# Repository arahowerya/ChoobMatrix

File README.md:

# ChoobMatrix
Source code for PIC16F722A nixie tube drivers

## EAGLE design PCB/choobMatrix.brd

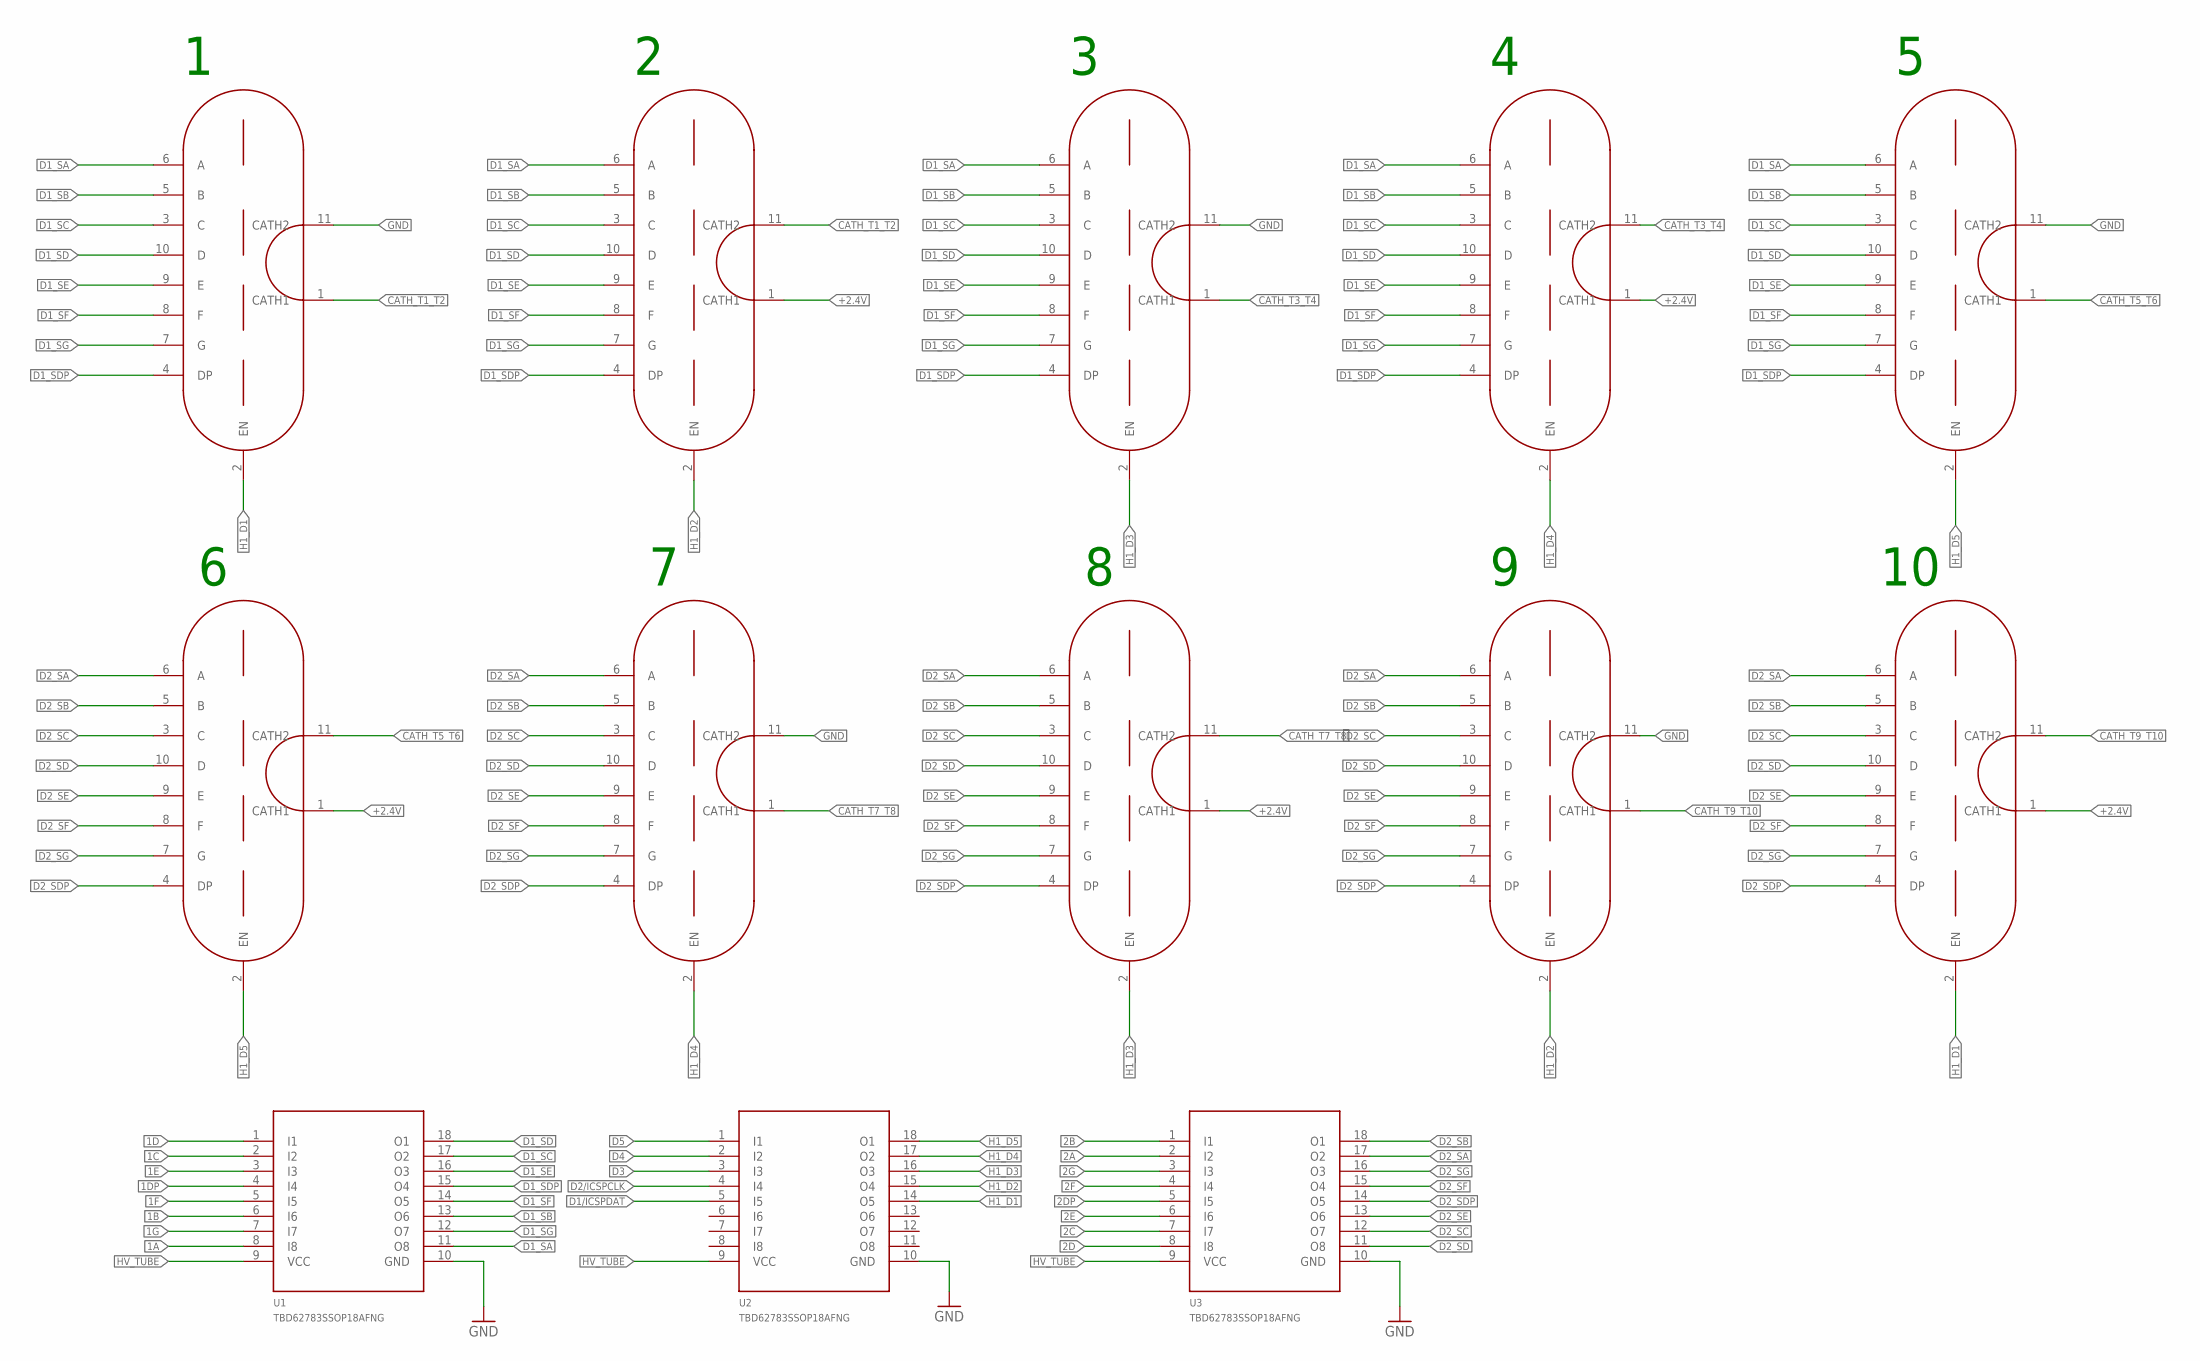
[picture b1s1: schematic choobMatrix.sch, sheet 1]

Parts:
T1, T2, T3, T4, T5, T6, T7, T8, T9, T10: IV11
U1, U2, U3: TBD62783SSOP18AFNG; SOP65P640X15-18

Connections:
1A: U1.8 (I8); also elsewhere on the board
1B: U1.6 (I6); also elsewhere on the board
1C: U1.2 (I2); also elsewhere on the board
1D: U1.1 (I1); also elsewhere on the board
1DP: U1.4 (I4); also elsewhere on the board
1E: U1.3 (I3); also elsewhere on the board
1F: U1.5 (I5); also elsewhere on the board
1G: U1.7 (I7); also elsewhere on the board
2A: U3.2 (I2); also elsewhere on the board
2B: U3.1 (I1); also elsewhere on the board
2C: U3.7 (I7); also elsewhere on the board
2D: U3.8 (I8); also elsewhere on the board
2DP: U3.5 (I5); also elsewhere on the board
2E: U3.6 (I6); also elsewhere on the board
2F: U3.4 (I4); also elsewhere on the board
2G: U3.3 (I3); also elsewhere on the board
+2.4V: T2.1 (CATH1), T4.1 (CATH1), T6.1 (CATH1), T8.1 (CATH1), T10.1 (CATH1); also elsewhere on the board
CATH_T1_T2: T1.1 (CATH1), T2.11 (CATH2)
CATH_T3_T4: T3.1 (CATH1), T4.11 (CATH2)
CATH_T5_T6: T5.1 (CATH1), T6.11 (CATH2)
CATH_T7_T8: T7.1 (CATH1), T8.11 (CATH2)
CATH_T9_T10: T9.1 (CATH1), T10.11 (CATH2)
D1/ICSPDAT: U2.5 (I5); also elsewhere on the board
D1_SA: T1.6 (A), T2.6 (A), T3.6 (A), T4.6 (A), T5.6 (A), U1.11 (O8)
D1_SB: T1.5 (B), T2.5 (B), T3.5 (B), T4.5 (B), T5.5 (B), U1.13 (O6)
D1_SC: T1.3 (C), T2.3 (C), T3.3 (C), T4.3 (C), T5.3 (C), U1.17 (O2)
D1_SD: T1.10 (D), T2.10 (D), T3.10 (D), T4.10 (D), T5.10 (D), U1.18 (O1)
D1_SDP: T1.4 (DP), T2.4 (DP), T3.4 (DP), T4.4 (DP), T5.4 (DP), U1.15 (O4)
D1_SE: T1.9 (E), T2.9 (E), T3.9 (E), T4.9 (E), T5.9 (E), U1.16 (O3)
D1_SF: T1.8 (F), T2.8 (F), T3.8 (F), T4.8 (F), T5.8 (F), U1.14 (O5)
D1_SG: T1.7 (G), T2.7 (G), T3.7 (G), T4.7 (G), T5.7 (G), U1.12 (O7)
D2/ICSPCLK: U2.4 (I4); also elsewhere on the board
D2_SA: T6.6 (A), T7.6 (A), T8.6 (A), T9.6 (A), T10.6 (A), U3.17 (O2)
D2_SB: T6.5 (B), T7.5 (B), T8.5 (B), T9.5 (B), T10.5 (B), U3.18 (O1)
D2_SC: T6.3 (C), T7.3 (C), T8.3 (C), T9.3 (C), T10.3 (C), U3.12 (O7)
D2_SD: T6.10 (D), T7.10 (D), T8.10 (D), T9.10 (D), T10.10 (D), U3.11 (O8)
D2_SDP: T6.4 (DP), T7.4 (DP), T8.4 (DP), T9.4 (DP), T10.4 (DP), U3.14 (O5)
D2_SE: T6.9 (E), T7.9 (E), T8.9 (E), T9.9 (E), T10.9 (E), U3.13 (O6)
D2_SF: T6.8 (F), T7.8 (F), T8.8 (F), T9.8 (F), T10.8 (F), U3.15 (O4)
D2_SG: T6.7 (G), T7.7 (G), T8.7 (G), T9.7 (G), T10.7 (G), U3.16 (O3)
D3: U2.3 (I3); also elsewhere on the board
D4: U2.2 (I2); also elsewhere on the board
D5: U2.1 (I1); also elsewhere on the board
GND: T1.11 (CATH2), T3.11 (CATH2), T5.11 (CATH2), T7.11 (CATH2), T9.11 (CATH2), U1.10 (GND), U2.10 (GND), U3.10 (GND); also elsewhere on the board
H1_D1: T1.2 (EN), T10.2 (EN), U2.14 (O5)
H1_D2: T2.2 (EN), T9.2 (EN), U2.15 (O4)
H1_D3: T3.2 (EN), T8.2 (EN), U2.16 (O3)
H1_D4: T4.2 (EN), T7.2 (EN), U2.17 (O2)
H1_D5: T5.2 (EN), T6.2 (EN), U2.18 (O1)
HV_TUBE: U1.9 (VCC), U2.9 (VCC), U3.9 (VCC); also elsewhere on the board

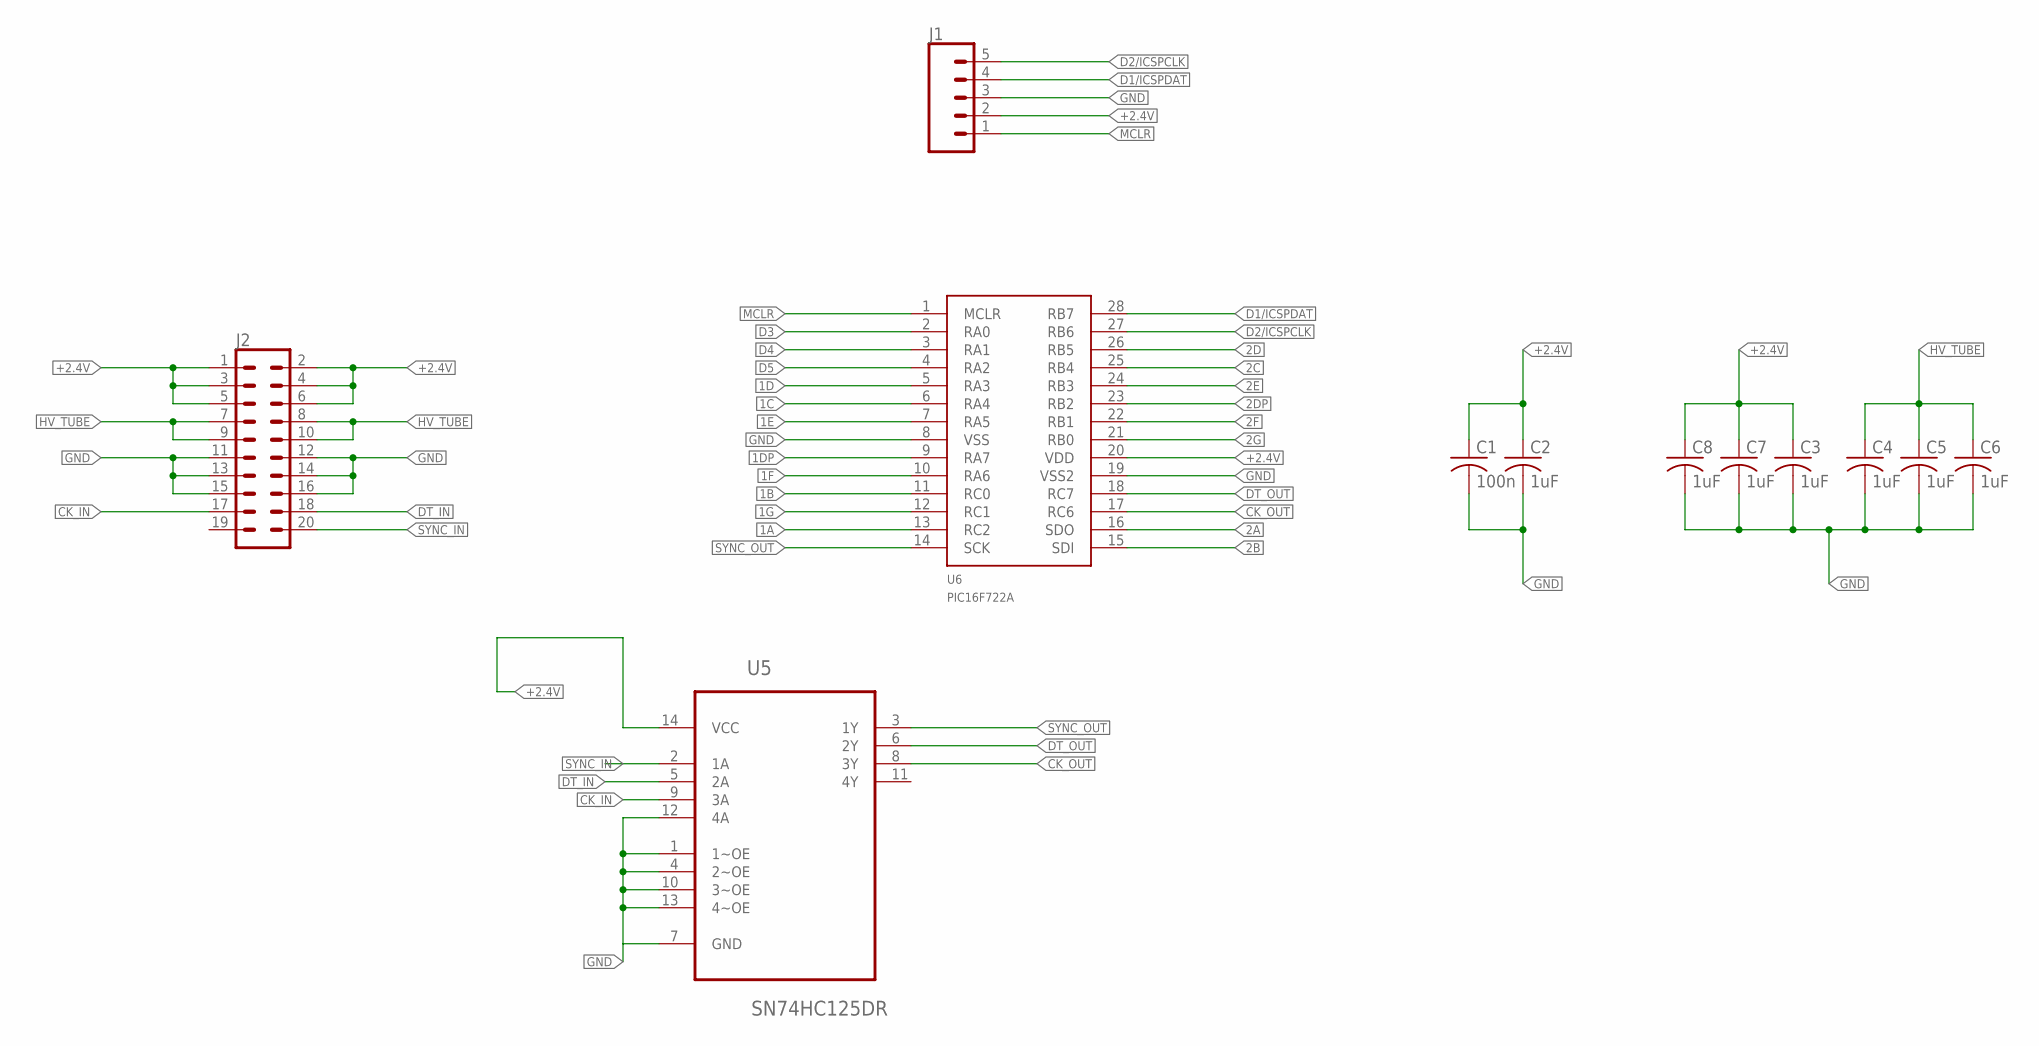
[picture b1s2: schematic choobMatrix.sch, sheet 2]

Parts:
C1: 100n; C0805K
C2, C3, C4, C5, C6, C7, C8: 1uF; C0805K
J1: CONN_05; 1X05
J2: CONN_10X2NOSILK; 2X10_NOSILK
U5: SN74HC125DR; SOIC127P600X175-14N
U6: PIC16F722A; SOP65P780X200-28N

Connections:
1A: U6.13 (RC2); also elsewhere on the board
1B: U6.11 (RC0); also elsewhere on the board
1C: U6.6 (RA4); also elsewhere on the board
1D: U6.5 (RA3); also elsewhere on the board
1DP: U6.9 (RA7); also elsewhere on the board
1E: U6.7 (RA5); also elsewhere on the board
1F: U6.10 (RA6); also elsewhere on the board
1G: U6.12 (RC1); also elsewhere on the board
2A: U6.16 (SDO); also elsewhere on the board
2B: U6.15 (SDI); also elsewhere on the board
2C: U6.25 (RB4); also elsewhere on the board
2D: U6.26 (RB5); also elsewhere on the board
2DP: U6.23 (RB2); also elsewhere on the board
2E: U6.24 (RB3); also elsewhere on the board
2F: U6.22 (RB1); also elsewhere on the board
2G: U6.21 (RB0); also elsewhere on the board
+2.4V: C1.1, C2.1, C3.1, C7.1, C8.1, J1.2, J2.1, J2.2, J2.3, J2.4, J2.5, J2.6, U5.14 (VCC), U6.20 (VDD); also elsewhere on the board
CK_IN: J2.17, U5.9 (3A)
CK_OUT: U5.8 (3Y), U6.17 (RC6)
D1/ICSPDAT: J1.4, U6.28 (RB7); also elsewhere on the board
D2/ICSPCLK: J1.5, U6.27 (RB6); also elsewhere on the board
D3: U6.2 (RA0); also elsewhere on the board
D4: U6.3 (RA1); also elsewhere on the board
D5: U6.4 (RA2); also elsewhere on the board
DT_IN: J2.18, U5.5 (2A)
DT_OUT: U5.6 (2Y), U6.18 (RC7)
GND: C1.2, C2.2, C3.2, C4.2, C5.2, C6.2, C7.2, C8.2, J1.3, J2.11, J2.12, J2.13, J2.14, J2.15, J2.16, U5.1 (1~OE), U5.4 (2~OE), U5.7 (GND), U5.10 (3~OE), U5.12 (4A), U5.13 (4~OE), U6.8 (VSS), U6.19 (VSS2); also elsewhere on the board
HV_TUBE: C4.1, C5.1, C6.1, J2.7, J2.8, J2.9, J2.10; also elsewhere on the board
MCLR: J1.1, U6.1 (MCLR)
SYNC_IN: J2.20, U5.2 (1A)
SYNC_OUT: U5.3 (1Y), U6.14 (SCK)

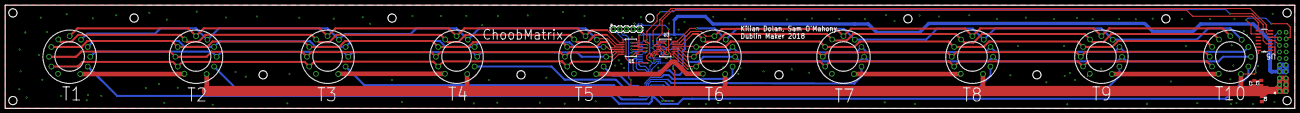
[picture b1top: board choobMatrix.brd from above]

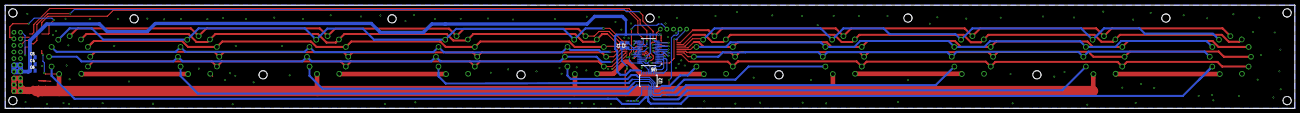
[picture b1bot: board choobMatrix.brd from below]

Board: 2 copper layers, 500.0 x 40.0 mm, 25 parts (7 on the bottom side), 57 nets.

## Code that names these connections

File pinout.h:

/* 
 * File:   pinout.h
 * Author: kilian
 *
 * Created on July 8, 2018, 1:05 PM
 */

#ifndef PINOUT_H
#define	PINOUT_H

#ifdef	__cplusplus
extern "C" {
#endif
#include <xc.h>


#define D1off do{PORTBbits.RB7 = 0;} while(PORTBbits.RB7 == 1)
#define D2off do{PORTBbits.RB6 = 0;} while(PORTBbits.RB6 == 1)
#define D3off do{PORTAbits.RA0 = 0;} while(PORTAbits.RA0 == 1)
#define D4off do{PORTAbits.RA1 = 0;} while(PORTAbits.RA1 == 1)
#define D5off do{PORTAbits.RA2 = 0;} while(PORTAbits.RA2 == 1)

#define D1on do{PORTBbits.RB7 = 1;} while(PORTBbits.RB7 == 0)
#define D2on do{PORTBbits.RB6 = 1;} while(PORTBbits.RB6 == 0)
#define D3on do{PORTAbits.RA0 = 1;} while(PORTAbits.RA0 == 0)
#define D4on do{PORTAbits.RA1 = 1;} while(PORTAbits.RA1 == 0)
#define D5on do{PORTAbits.RA2 = 1;} while(PORTAbits.RA2 == 0)
    
#define S1Aon do{PORTCbits.RC2 = 1;} while(PORTCbits.RC2 == 0)
#define S1Bon do{PORTCbits.RC0 = 1;} while(PORTCbits.RC0 == 0)
#define S1Con do{PORTAbits.RA4 = 1;} while(PORTAbits.RA4 == 0)
#define S1Don do{PORTAbits.RA3 = 1;} while(PORTAbits.RA3 == 0)
#define S1Eon do{PORTAbits.RA5 = 1;} while(PORTAbits.RA5 == 0)
#define S1Fon do{PORTAbits.RA6 = 1;} while(PORTAbits.RA6 == 0)
#define S1Gon do{PORTCbits.RC1 = 1;} while(PORTCbits.RC1 == 0)
#define S1DPon do{PORTAbits.RA7 = 1;} while(PORTAbits.RA7 == 0)
    
#define S2Aon do{PORTCbits.RC5 = 1;} while(PORTCbits.RC5 == 0)
#define S2Bon do{PORTCbits.RC4 = 1;} while(PORTCbits.RC4 == 0)
#define S2Con do{PORTBbits.RB4 = 1;} while(PORTBbits.RB4 == 0)
#define S2Don do{PORTBbits.RB5 = 1;} while(PORTBbits.RB5 == 0)
#define S2Eon do{PORTBbits.RB3 = 1;} while(PORTBbits.RB3 == 0)
#define S2Fon do{PORTBbits.RB1 = 1;} while(PORTBbits.RB1 == 0)
#define S2Gon do{PORTBbits.RB0 = 1;} while(PORTBbits.RB0 == 0)
#define S2DPon do{PORTBbits.RB2 = 1;} while(PORTBbits.RB2 == 0)


#define S1Aoff do{PORTCbits.RC2 = 0;} while(PORTCbits.RC2 == 1)
#define S1Boff do{PORTCbits.RC0 = 0;} while(PORTCbits.RC0 == 1)
#define S1Coff do{PORTAbits.RA4 = 0;} while(PORTAbits.RA4 == 1)
#define S1Doff do{PORTAbits.RA3 = 0;} while(PORTAbits.RA3 == 1)
#define S1Eoff do{PORTAbits.RA5 = 0;} while(PORTAbits.RA5 == 1)
#define S1Foff do{PORTAbits.RA6 = 0;} while(PORTAbits.RA6 == 1)
#define S1Goff do{PORTCbits.RC1 = 0;} while(PORTCbits.RC1 == 1)
#define S1DPoff do{PORTAbits.RA7 = 0;} while(PORTAbits.RA7 == 1)
    
#define S2Aoff do{PORTCbits.RC5 = 0;} while(PORTCbits.RC5 == 1)
#define S2Boff do{PORTCbits.RC4 = 0;} while(PORTCbits.RC4 == 1)
#define S2Coff do{PORTBbits.RB4 = 0;} while(PORTBbits.RB4 == 1)
#define S2Doff do{PORTBbits.RB5 = 0;} while(PORTBbits.RB5 == 1)
#define S2Eoff do{PORTBbits.RB3 = 0;} while(PORTBbits.RB3 == 1)
#define S2Foff do{PORTBbits.RB1 = 0;} while(PORTBbits.RB1 == 1)
#define S2Goff do{PORTBbits.RB0 = 0;} while(PORTBbits.RB0 == 1)
#define S2DPoff do{PORTBbits.RB2 = 0;} while(PORTBbits.RB2 == 1)


#ifdef	__cplusplus
}
#endif

#endif	/* PINOUT_H */

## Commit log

2018-07-10 Changing to xc8 v1.45 and removing bugs
2018-07-10 Tidying up files and attempting a blinky LED on RA1 - no luck yet...
2018-07-10 Updating README with pinout
2018-07-11 Added AUSART code for data interrupt setup and handling - some compile issues
2018-07-11 Fixed code errors - now compiles
2018-07-12 Blinky LED's and asynchronous UART now working. Woop!
2018-07-13 Added 9-bit address mode comments. General tidy up.
2018-07-16 code for driving basic display (with counter)
2018-07-16 new gitignore
2018-07-16 removing files
2018-07-16 Different config word setup
2018-07-16 comments
2018-07-16 Timer 2 init
2018-07-16 Pushing clean branch with lastest UART message parsing/displaying updates
2018-07-17 updating gitignore
2018-07-17 deleting unnessecary files
2018-07-17 Updated UART baud rate generator
2018-07-18 PIC set up for 8MHz clock and Async UART
2018-07-18 display driver, running at 16MHz and being driven off timer1
2018-07-18 removing ghosting and tidying
2018-07-19 mux frequency minimums
2018-07-20 First run of showcase code for each slave - still testing
2018-07-20 ITS FUCKING WORKING
2018-07-20 Minor updates - fixed warnings and removed some redundant code
2018-08-16 Moving to Subfolder
2018-08-16 Combining repos
2018-08-16 cleaning up
2018-08-16 Adding PCB files
2018-08-16 Processing Animations
2018-08-16 removing submodule

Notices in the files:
parts and their libraries:
SparkFun-Connectors: Licensing: Creative Commons ShareAlike 4.0 International - https://creativecommons.org/licenses/by-sa/4.0
